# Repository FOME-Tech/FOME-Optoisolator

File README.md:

# rusEFI-Optoisolator
 Simple module to use the negative side of a coil and a trigger input for fuel only rusEFI

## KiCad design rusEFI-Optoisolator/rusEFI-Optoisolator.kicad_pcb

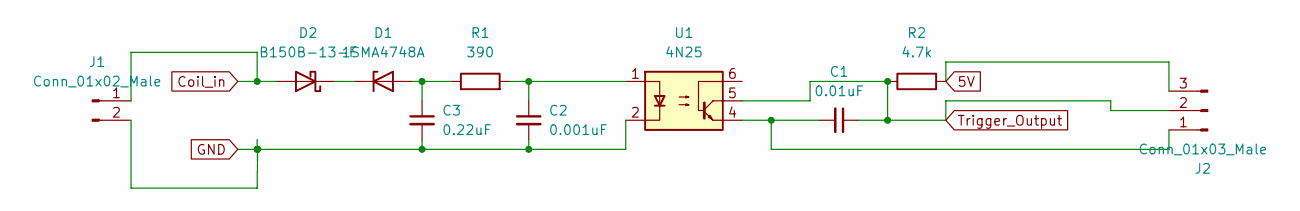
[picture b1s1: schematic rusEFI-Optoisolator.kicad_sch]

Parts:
C1: 0.01uF; C_0805_2012Metric; LCSC C469523
C2: 0.001uF; C_1206_3216Metric; LCSC C77494
C3: 0.22uF; C_1206_3216Metric; LCSC C77494
D1: 1SMA4748A; D_SMA; LCSC C2903856
D2: B150B-13-F; D_SMB; LCSC C134432
J1: Conn_01x02_Male; PinHeader_1x02_P2.54mm_Vertical
J2: Conn_01x03_Male; PinHeader_1x03_P2.54mm_Vertical
R1: 390; R_Axial_DIN0207_L6.3mm_D2.5mm_P15.24mm_Horizontal; LCSC C2759146
R2: 4.7k; R_0805_2012Metric; LCSC C2907326
U1: 4N25; DIP-6_W7.62mm; LCSC C3008818

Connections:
5V: J2.3, R2.2
Coil_in: D2.2 (A), J1.1
GND: C2.2, C3.2, J1.2, U1.2
unnamed: C1.2, J2.1, U1.4
unnamed: C2.1, R1.2, U1.1
unnamed: C3.1, D1.2 (A), R1.1
unnamed: D1.1 (K), D2.1 (K)
Trigger_Output: C1.1, J2.2, R2.1, U1.5

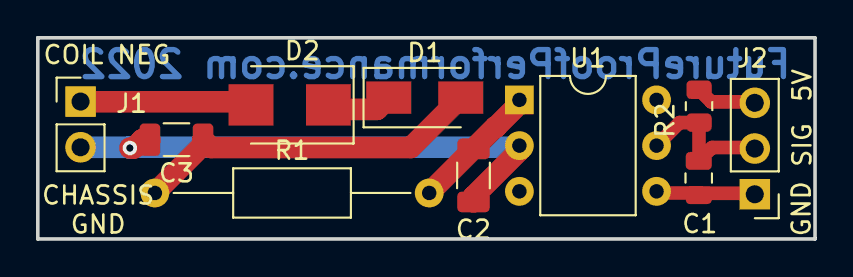
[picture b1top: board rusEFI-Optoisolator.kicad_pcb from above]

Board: 2 copper layers, 43.2 x 11.2 mm, 10 parts (0 on the bottom side), 8 nets.

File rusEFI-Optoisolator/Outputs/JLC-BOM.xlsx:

Comment | Designator | Footprint | LCSC Part Number
0.0022uF1 | C2 | C_1206_3216Metric | C77494
390 | R1 | R_1206_3216Metric | C25378
4.7k | R2 | R_0805_2012Metric | C17673
0.01uF | C1 | C_0805_2012Metric | C469523
B150B-13-F | D2 | D_SMB | C134432
4N25 | U1 | DIP-6_W7.62mm | C191858
1SMA4748A | D4 | D_SMA | C2690205

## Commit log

2022-09-12 First draft of board
2022-09-12 Updates, gerbers and bom files.
2022-10-09 New version
2022-11-21 Updated before order
